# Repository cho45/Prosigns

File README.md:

"Prosigns" USB CW Interface
===========================

"Prosigns" is a USB CW (Morse) interface written with AVR V-SUB for ham radio with following features:

 * Automatic keying from host computer
 * Manual keying by paddles with elekey
 * Analyze manual keying and decode it

## Directory Structure

 * circuit -> Include [Eagle][1] circuit file (and board)
 * firmware -> firmware

[1]: http://www.cadsoftusa.com/

## Development

### Install dependency

- [CrossPack AVR for Mac OS X]( http://www.obdev.at/products/crosspack/index.html )

### Programming to chip

```
cd firmware
make install # write fuse and program
```

```
make flash # only write program
```

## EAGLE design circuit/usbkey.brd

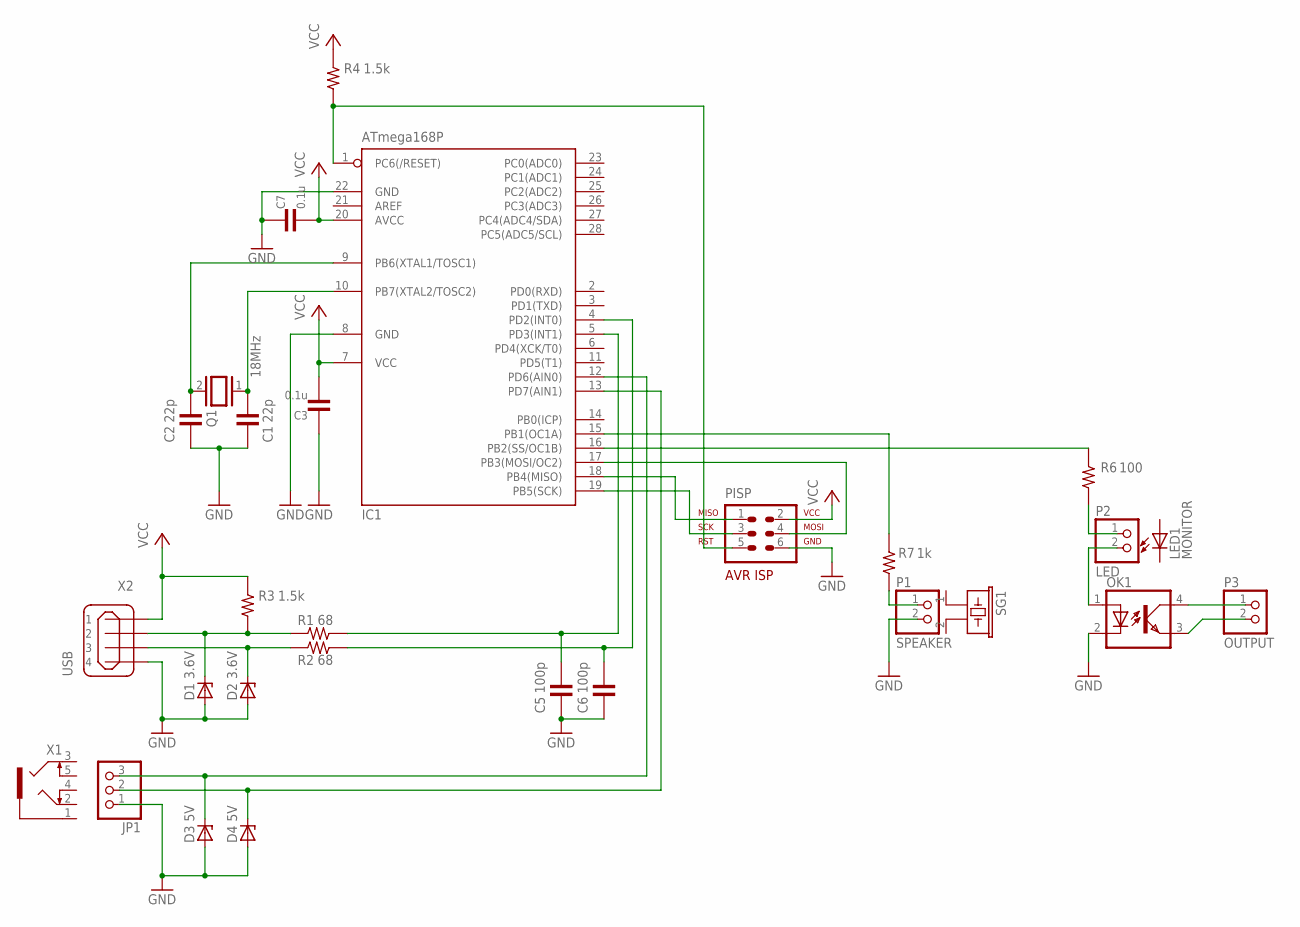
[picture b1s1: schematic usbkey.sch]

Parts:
C1, C2: 22p; 50-0302-2.54
C3, C7: 0.1u; 50-0302-2.54
C5, C6: 100p; 50-0302-2.54
D1, D2: 3.6V; DO35Z10
D3, D4: 5V; DO35Z10
IC1: ATmega168P; DIL28-3
JP1: PINHD-1X3; 1X03
LED1: MONITOR; LED3MM
OK1: LTV816; DIL04
P1: SPEAKER; 1X02
P2: LED; 1X02
P3: OUTPUT; 1X02
PISP: AVR-ISP-6VERT; AVR-ISP-6
Q1: 18MHz; QS
R1, R2: 68; 1/4W-2.54V
R3: 1.5k; 1/4W-7.62H
R4: 1.5k; 1/4W-2.54V
R6: 100; 1/4W-7.62H
R7: 1k; 1/4W-7.62H
SG1: EFBRD22C41
X1: 1503_09
X2: USB; 85-32004-10X

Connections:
GND: C1.PAD2 (2), C2.PAD2 (2), C3.PAD1 (1), C5.PAD2 (2), C6.PAD2 (2), C7.PAD1 (1), D1.A, D2.A, D3.A, D4.A, IC1.8 (GND), IC1.22 (GND), JP1.1, OK1.2 (C), P1.2, PISP.6, X2.4
unnamed: C1.PAD1 (1), IC1.10 (PB7(XTAL2/TOSC2)), Q1.1
unnamed: C2.PAD1 (1), IC1.9 (PB6(XTAL1/TOSC1)), Q1.2
unnamed: C5.PAD1 (1), IC1.5 (PD3(INT1)), R1.PAD2 (2)
unnamed: D2.C, R2.PAD1 (1), X2.3
unnamed: C6.PAD1 (1), IC1.4 (PD2(INT0)), R2.PAD2 (2)
unnamed: D1.C, R1.PAD1 (1), R3.PAD1 (1), X2.2
unnamed: D3.C, IC1.12 (PD6(AIN0)), JP1.3
unnamed: D4.C, IC1.13 (PD7(AIN1)), JP1.2
unnamed: IC1.1 (PC6(/RESET)), PISP.5, R4.PAD1 (1)
unnamed: IC1.17 (PB3(MOSI/OC2)), PISP.4
unnamed: IC1.19 (PB5(SCK)), PISP.3
unnamed: IC1.18 (PB4(MISO)), PISP.1
unnamed: P2.1, R6.PAD1 (1)
unnamed: P1.1, R7.PAD1 (1)
unnamed: IC1.15 (PB1(OC1A)), R7.PAD2 (2)
unnamed: IC1.16 (PB2(SS/OC1B)), R6.PAD2 (2)
unnamed: OK1.1 (A), P2.2
OUT+: OK1.4 (COL), P3.1
OUT-: OK1.3 (EMIT), P3.2
VCC: C3.PAD2 (2), C7.PAD2 (2), IC1.7 (VCC), IC1.20 (AVCC), PISP.2, R3.PAD2 (2), R4.PAD2 (2), X2.1

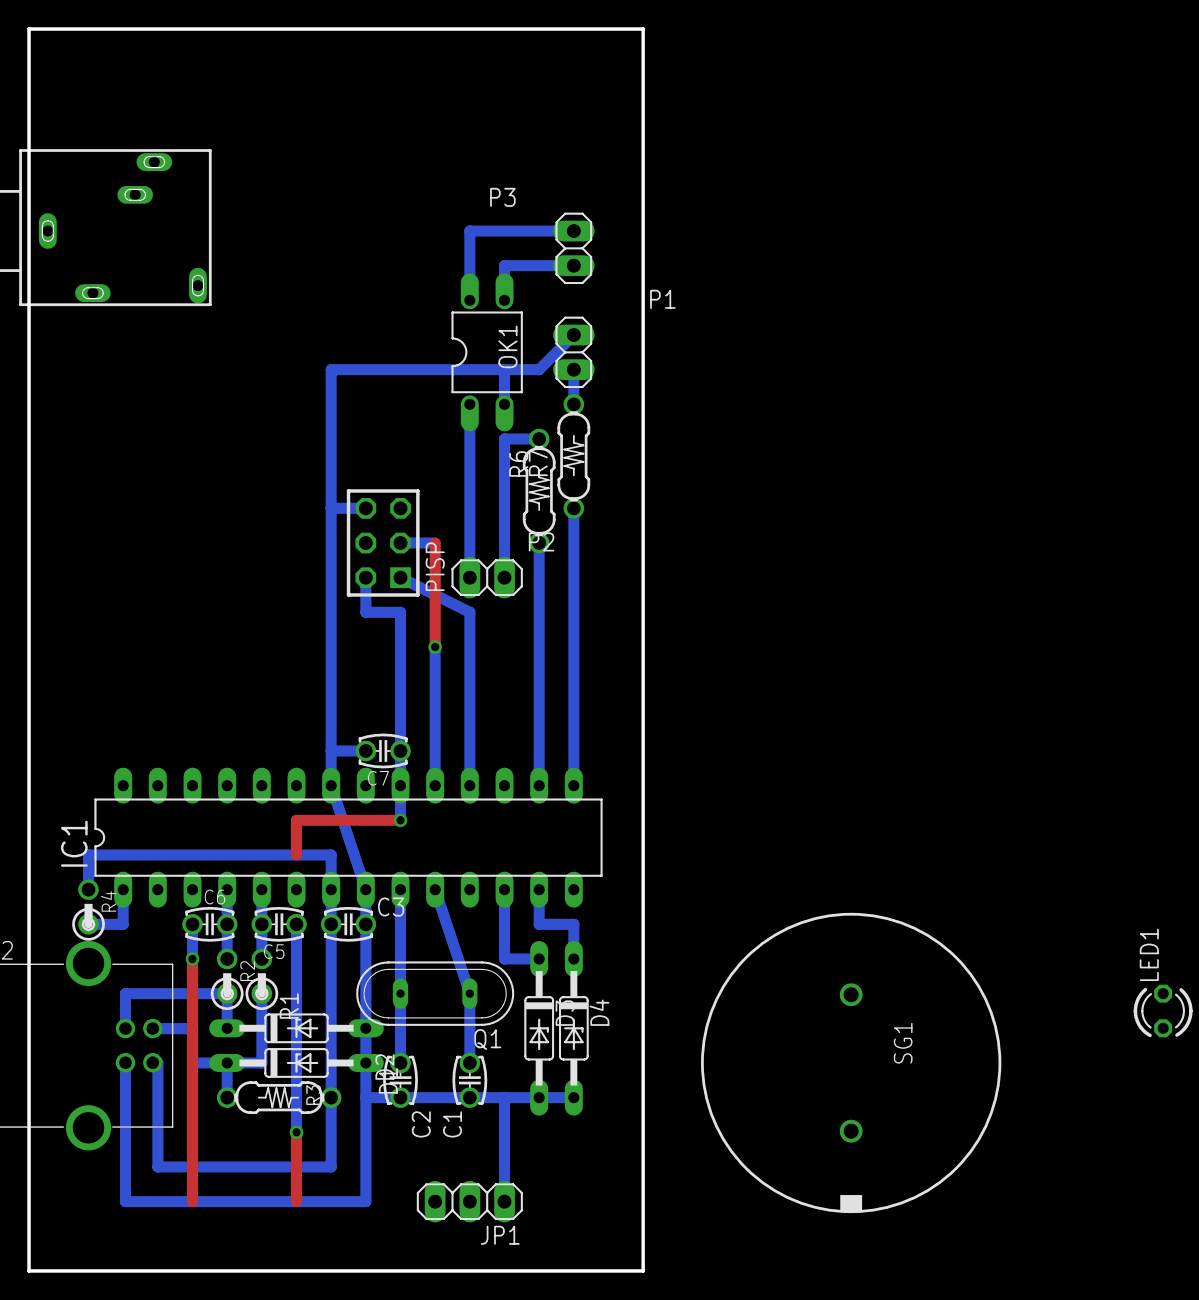
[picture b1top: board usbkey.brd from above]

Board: 2 copper layers, 45.0 x 91.0 mm, 28 parts (0 on the bottom side), 21 nets.

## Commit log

2013-10-20 interrupt_transfer
2013-10-20 claim_interface can not be used in Mac OS + libusb, just use only control_transfer
2013-10-20 more stable timer
2013-10-21 16MHz で安定させるために電源を5Vに。USB のレベルはツェナーダイオードで低電圧化
2013-10-21 iupdate
2013-10-25 change port
2013-10-25 電圧あげたら STALL しなくなったので精度をあげた
2013-10-25 cw shell
2013-10-25 paddle
2013-10-25 STALL する……
2013-10-26 頻度調整
2013-10-26 backspace
2013-10-26 prosignes
2013-10-27 debug
2013-10-27 oh...
2013-11-02 eagle
2014-07-13 chrome.usb work
2014-07-15 inhibit
2014-07-15 F_CPU 18MHz
2014-07-16 restructure
2014-07-17 reset の 0.1u は ISP ができなくなる
2014-07-18 driver
2014-07-18 update eeprom read
2014-07-19 driver ruby
2014-07-19 WebSocket server
2014-09-02 clib
